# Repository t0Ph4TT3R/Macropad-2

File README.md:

# Macropad-2
This is a new version of a macropad for hackpad event at Hack club. I made it knowing what worked and didn't from a previous time, and it should be more polished!

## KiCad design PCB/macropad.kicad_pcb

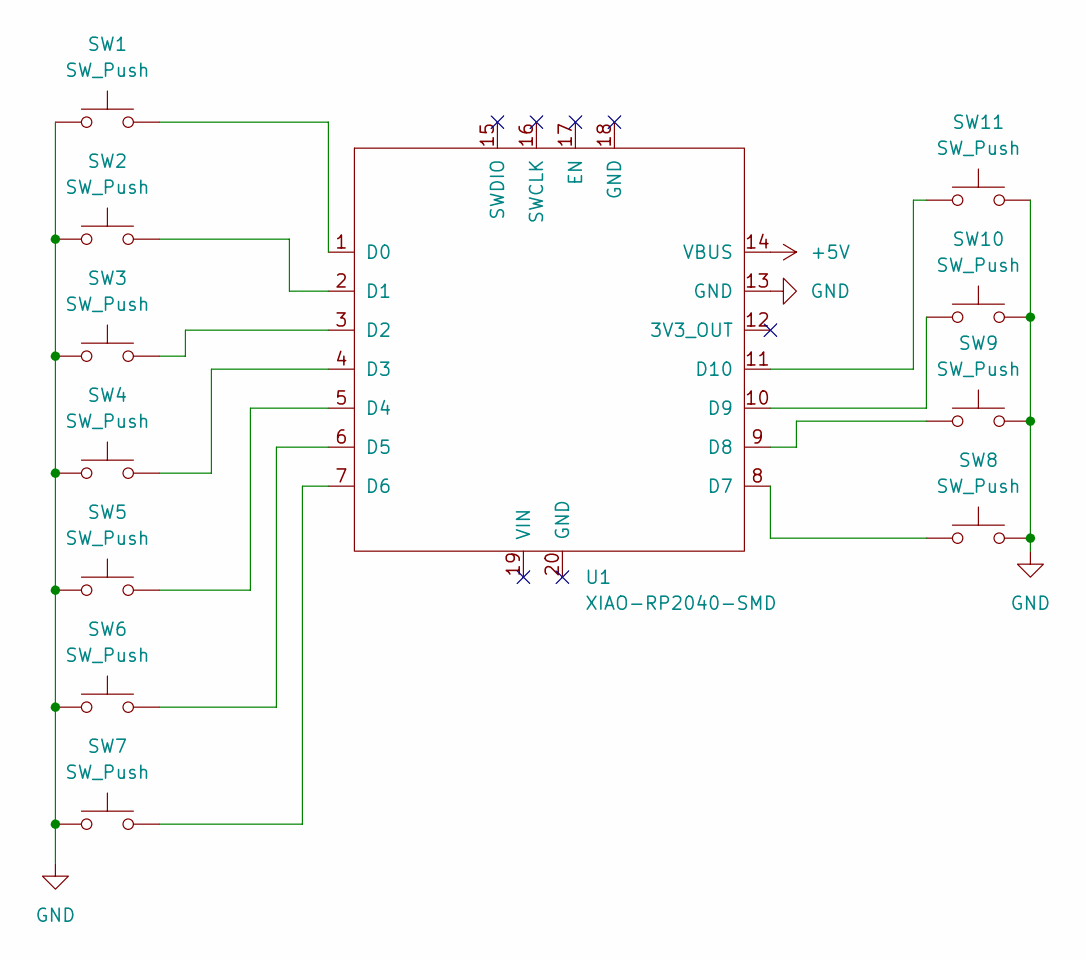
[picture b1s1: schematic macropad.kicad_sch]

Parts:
SW1, SW2, SW3, SW4, SW5, SW6, SW7, SW8, SW9, SW10, SW11: SW_Push; SW_Cherry_MX_1.00u_PCB
U1: XIAO-RP2040-SMD; XIAO-RP2040-DIP

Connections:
+5V: U1.14 (VBUS)
GND: SW1.1, SW2.1, SW3.1, SW4.1, SW5.1, SW6.1, SW7.1, SW8.2, SW9.2, SW10.2, SW11.2, U1.13 (GND)
unnamed: SW1.2, U1.1 (D0)
unnamed: SW2.2, U1.2 (D1)
unnamed: SW3.2, U1.3 (D2)
unnamed: SW4.2, U1.4 (D3)
unnamed: SW5.2, U1.5 (D4)
unnamed: SW6.2, U1.6 (D5)
unnamed: SW7.2, U1.7 (D6)
unnamed: SW8.1, U1.8 (D7)
unnamed: SW9.1, U1.9 (D8)
unnamed: SW10.1, U1.10 (D9)
unnamed: SW11.1, U1.11 (D10)

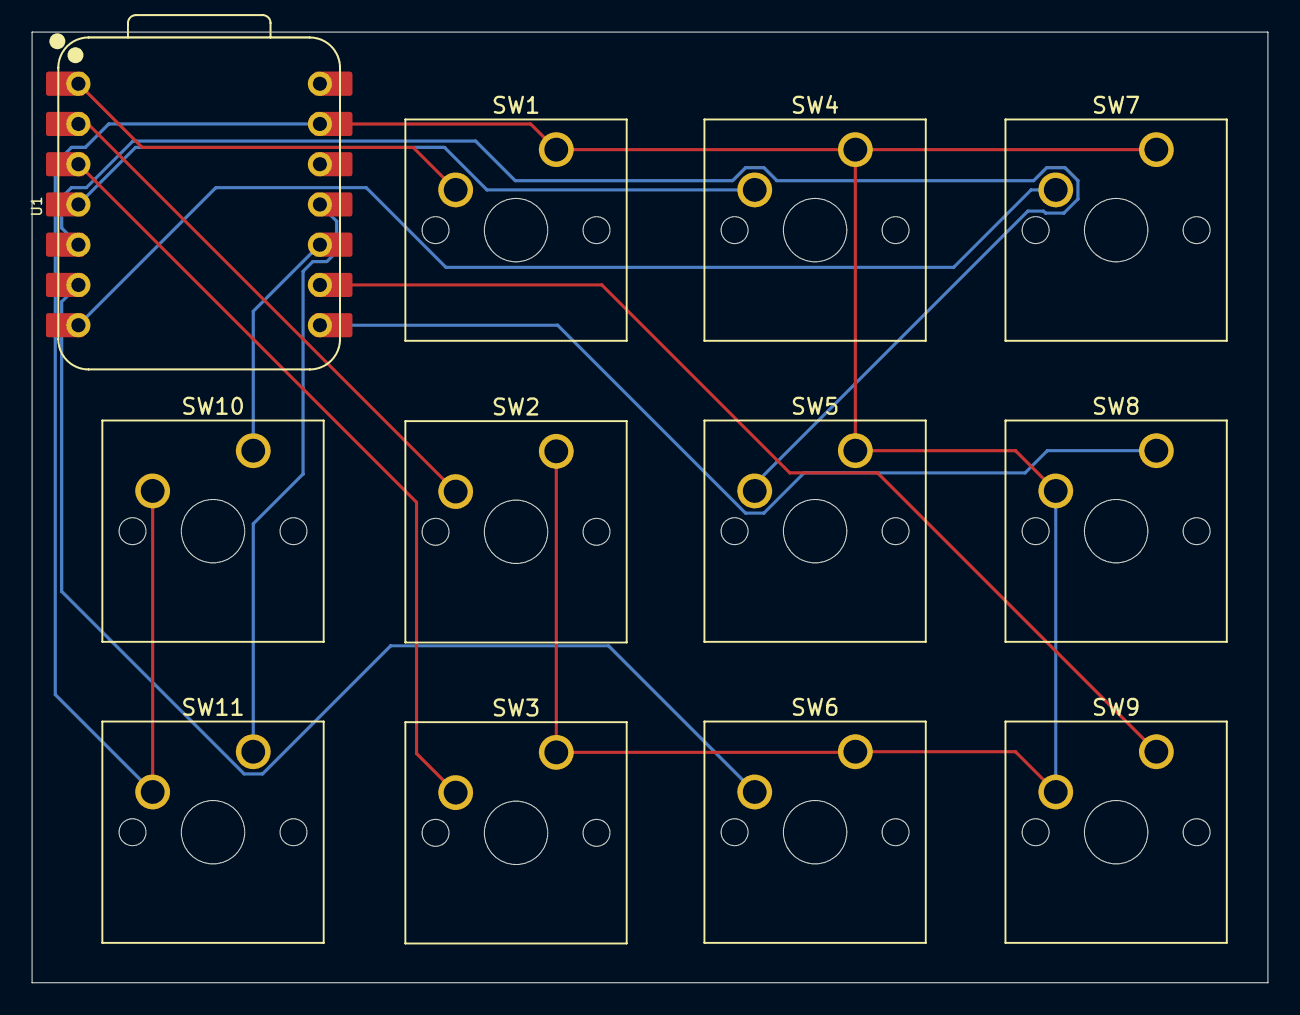
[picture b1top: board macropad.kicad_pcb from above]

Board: 2 copper layers, 78.0 x 60.0 mm, 12 parts (0 on the bottom side), 12 nets.
